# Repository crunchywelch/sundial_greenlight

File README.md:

# Sundial Greenlight

Terminal-based QC (Quality Control) application for audio cable testing and inventory management.

## Quick Start

### Setup Virtual Environment

```bash
# IMPORTANT: Must be SOURCED, not executed!
source dev_env.sh
```

**Why source instead of execute?**
- Running `./dev_env.sh` activates the venv in a subshell that closes immediately
- Sourcing with `source dev_env.sh` activates it in your current shell session

### Run the Application

```bash
python -m greenlight.main
```

On startup:
1. Splash screen displays with operator list
2. Select your operator number
3. You land on the scan hub: scan a cable to look it up or test it, or press
   a key for intake, inventory, orders, registration codes and labels

### Deactivate Virtual Environment

```bash
deactivate
```

## Features

### Cable Intake
Record pre-labelled cables against a SKU (press `r` at the scan hub):
1. Choose cable type (series → pattern → length → connector, or MISC/LTD)
2. Scan barcode with Zebra DS2208 scanner
3. Confirm serial number on screen
4. Press Enter to save to database
5. Scanner ready for next cable
6. Type 'q' + Enter to finish and see summary

### Test Cables
Scan a cable at the hub to run QC tests:
- Arduino-based electrical testing (continuity, resistance, XLR shell bond)
- Automatic pass/fail determination
- Results saved to database

### Other Features
- **Inventory** dashboard, LTD editions, dealer stock
- **Orders**: customer lookup and order fulfillment
- **Wholesale** registration codes, wire labels, box/UPC labels

## Repository Layout

| Path | What lives there |
|---|---|
| `greenlight/` | The terminal app |
| `shopify_app/` | Shopify Remix app + extensions |
| `catalog/` | Hand-edited product catalog YAML (the source of truth) |
| `data/` | Generated output and vendor input files |
| `tools/` | Admin and back-office scripts, grouped by area |
| `tests/` | SKU parity test + fixtures; `integration/` hits live services |
| `services/` | systemd units |
| `arduino/`, `ArduinoApps/` | Cable tester firmware and hardware docs |

## Testing

```bash
pytest                               # Python tests, no DB or network needed
(cd shopify_app && npm test)         # JS resolver against the same fixtures
```

Scripts in `tests/integration/` write to the live database / Shopify, so
pytest skips them unless `GREENLIGHT_RUN_INTEGRATION=1` is set. Read them
before running.

## Testing the Scanner

```bash
python tools/scanner/scantest.py
```

## Database Setup

See `tools/audio/schema.sql` for the database schema.

## Configuration

Edit `.env` for database settings and hardware flags (`GREENLIGHT_*`).
Operators are listed in `greenlight/config.py`.

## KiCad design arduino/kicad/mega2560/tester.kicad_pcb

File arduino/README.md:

# Arduino Cable Tester

This directory contains the Arduino firmware for the Greenlight Cable Testing system.

## Files

### Main Firmware
- **`cable_tester.ino`** - Complete Arduino sketch for ATmega32
- **`CableTester.h`** - Arduino library header (for future modular development)

### Documentation  
- **`HARDWARE_SETUP.md`** - Detailed hardware requirements and circuit diagrams
- **`README.md`** - This file

## Quick Start

### 1. Hardware Setup
1. Connect Arduino Mega 2560 to Raspberry Pi via USB
2. Build test circuit according to `HARDWARE_SETUP.md`
3. Connect cable test fixture to designated pins

### 2. Upload Firmware
**Using arduino-cli (Recommended):**
```bash
cd arduino
arduino-cli compile --fqbn arduino:avr:mega cable_tester
arduino-cli upload -p /dev/ttyACM0 --fqbn arduino:avr:mega cable_tester
```

**Using Arduino IDE:**
1. Open `cable_tester/cable_tester.ino` in Arduino IDE
2. Select Board: "Arduino Mega or Mega 2560"
3. Select correct COM port: /dev/ttyACM0
4. Click Upload

### 3. Test Communication
1. Open Serial Monitor (9600 baud)
2. Send command: `GET_UNIT_ID`
3. Should receive: `UNIT_ID:1`
4. Send command: `GET_STATUS`
5. Should receive: `STATUS:READY:FIXTURE_EMPTY:VOLTAGE_X.XX`

## Supported Commands

| Command | Description | Response |
|---------|-------------|----------|
| `GET_UNIT_ID` | Get Arduino unit identifier | `UNIT_ID:1` |
| `GET_STATUS` | Get system status | `STATUS:READY:FIXTURE_EMPTY:VOLTAGE_4.98` |
| `TEST_CABLE` | Run complete cable test | `TEST_RESULT:CONTINUITY:1:RESISTANCE:0.245:CAPACITANCE:156.2:POLARITY:1:OVERALL:1` |
| `CALIBRATE` | Run calibration sequence | `CALIBRATION:COMPLETE:VOLTAGE_CAL:1.0023:...` |
| `RESET` | Reset test circuit | `RESET:COMPLETE` |
| `SELF_TEST` | Run power-on self test | `SELF_TEST:PASS:VOLTAGE:4.98` |

## Test Result Format

The Arduino returns test results in a structured format:

```
TEST_RESULT:CONTINUITY:1:RESISTANCE:0.245:CAPACITANCE:156.2:POLARITY:1:OVERALL:1
```

**Fields:**
- **CONTINUITY**: 1 = all connections good, 0 = open circuit detected
- **RESISTANCE**: DC resistance in ohms (e.g., 0.245Ω)  
- **CAPACITANCE**: Cable capacitance in picofarads (e.g., 156.2pF)
- **POLARITY**: 1 = correct, 0 = reversed
- **OVERALL**: 1 = pass, 0 = fail

## Hardware Requirements

### Arduino Board
- **Arduino Mega 2560 R3** (official or compatible clone)
- Built-in USB connection (no external adapter needed)
- Provides excellent memory headroom:
  - 253KB Flash (4% used)
  - 8KB RAM (21% used)
  - 54 Digital I/O pins
  - 16 Analog inputs

### Circuit Components
- 3x 5V SPDT relays (continuity switching)
- Basic test circuit (see HARDWARE_SETUP.md)
- 4x LEDs for status indication
- Cable test fixture with insertion detection

### Recommended Components
- Precision current source for resistance measurement
- RC timing circuit for capacitance measurement
- Voltage reference for calibration
- ESD protection on all inputs

## Calibration

### Automatic Calibration
1. Send `CALIBRATE` command
2. Follow prompts for short circuit and open circuit connections
3. Calibration values are automatically calculated and stored

### Manual Calibration Values
You can adjust these constants in the code if needed:
```cpp
const float CONTINUITY_THRESHOLD_OHMS = 5.0;
const float VOLTAGE_REF = 5.0;
const float TEST_CURRENT_MA = 1.0;
```

## Troubleshooting

### No Response from Arduino
- Check USB connection and COM port
- Verify 9600 baud rate in Serial Monitor
- Check power LED on Arduino board

### Incorrect Test Results
- Run `SELF_TEST` command to verify hardware
- Check test fixture connections
- Run `CALIBRATE` to update calibration values
- Verify relay operation with multimeter

### Communication Errors
- Ensure clean 5V power supply
- Check for electrical noise interference  
- Verify all ground connections
- Consider USB isolation if needed

## Integration with Raspberry Pi

The Arduino communicates with the Raspberry Pi via USB serial. The Python code in the main project handles:

- Automatic Arduino detection on `/dev/ttyUSB*` ports
- Command/response protocol implementation
- Error handling and retries
- Integration with the Greenlight Terminal UI

## Development Notes

### Adding New Test Functions
1. Add command handling in `handleSerialCommand()`
2. Implement test function following existing patterns
3. Update response format documentation
4. Test with Python integration code

### Modifying Pin Assignments
1. Update pin definitions at top of `cable_tester.ino`
2. Update `HARDWARE_SETUP.md` documentation
3. Verify no pin conflicts with Arduino requirements

### Performance Optimization
- Adjust `MEASUREMENT_SAMPLES` for speed vs accuracy trade-off
- Modify delay times in test sequences as needed
- Consider interrupt-driven communication for faster response

## Production Deployment

### Quality Control
- Verify calibration accuracy with known standards
- Test all relay operations under load
- Validate measurement ranges with precision instruments
- Perform temperature stability testing

### Maintenance
- Monthly calibration verification
- Semi-annual precision component check  
- Annual full system validation
- Keep spare Arduino programmed and ready

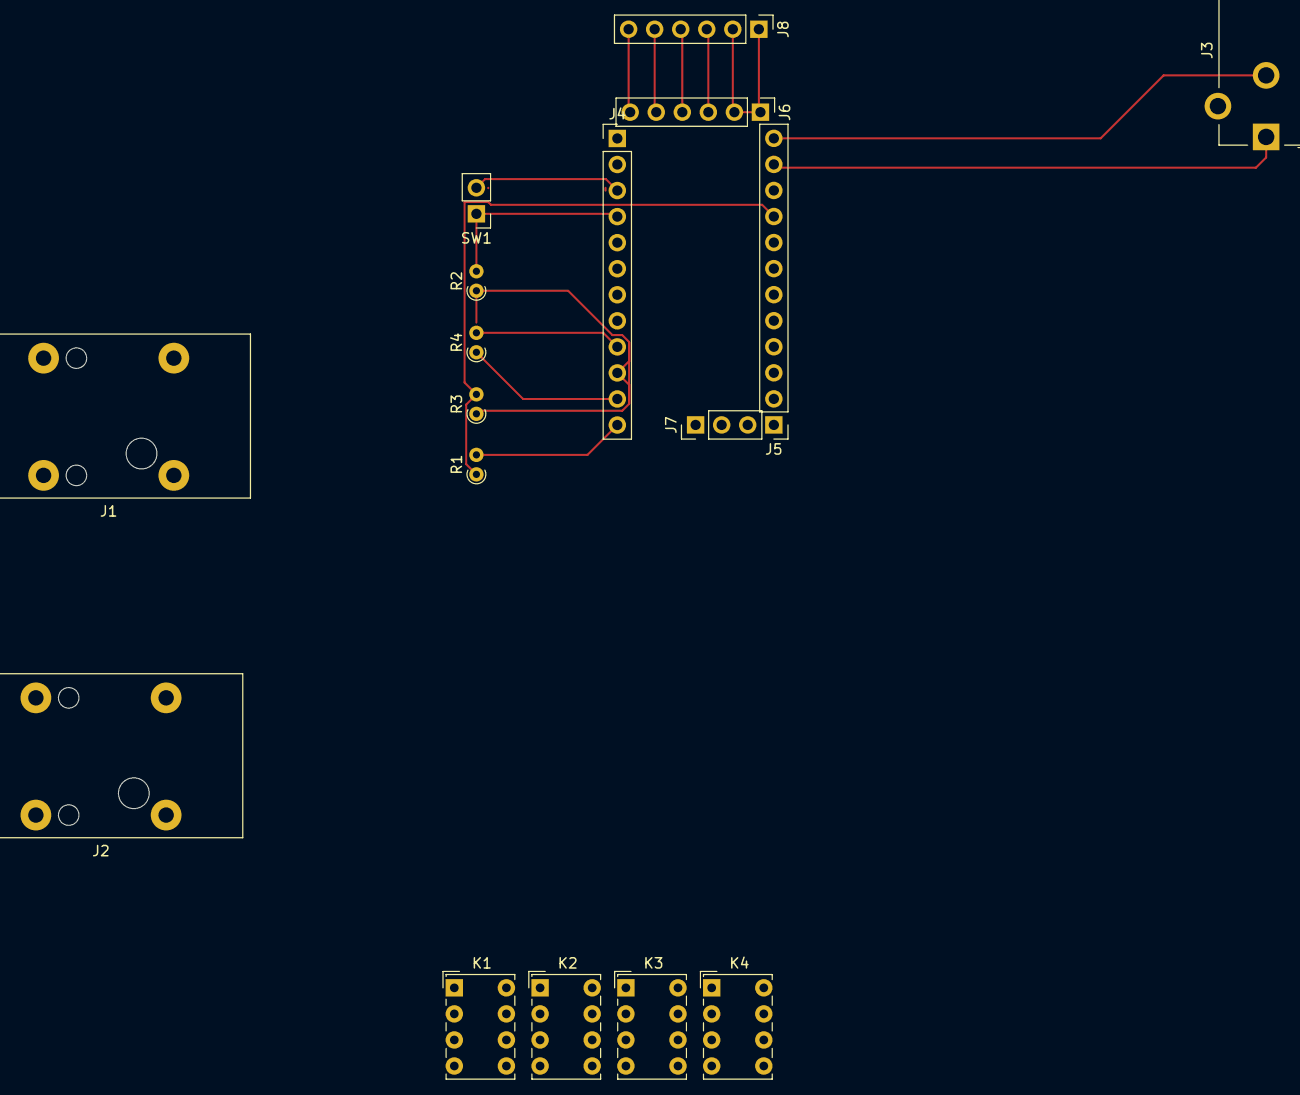
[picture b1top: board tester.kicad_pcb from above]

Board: 2 copper layers, 17 parts (0 on the bottom side), 12 nets.

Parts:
J1, J2: AudioJack2; Jack_6.35mm_Neutrik_NRJ4HF_Horizontal
J3: Barrel_Jack; BarrelJack_CUI_PJ-102AH_Horizontal
J4, J5: Conn_01x12; PinHeader_1x12_P2.54mm_Vertical
J6: Conn_01x06; PinHeader_1x06_P2.54mm_Vertical
J7: Conn_01x03; PinHeader_1x03_P2.54mm_Vertical
J8: Conn_01x06_Pin; PinHeader_1x06_P2.54mm_Vertical
K1, K2, K3, K4: Relay_DPDT; Relay_DPDT_Omron_G6K-2P
R1, R4: R10K; R_Axial_DIN0204_L3.6mm_D1.6mm_P1.90mm_Vertical
R2: R3.1K; R_Axial_DIN0204_L3.6mm_D1.6mm_P1.90mm_Vertical
R3: R1.8k; R_Axial_DIN0204_L3.6mm_D1.6mm_P1.90mm_Vertical
SW1: SW_Push; PinHeader_1x02_P2.54mm_Vertical

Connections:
/D6: J4.9, R4.2
/D7: J4.10, R2.1, R3.1
/D8: J4.11, R4.1
/DTR: J6.6, J8.6
/GND: J4.4, J6.1, J6.2, J8.1, J8.2, R2.2, SW1.1
/RST: J4.3, SW1.2
/RX1: J6.4, J8.4
/TX0: J6.5, J8.5
/VCC: J5.9, J6.3, J8.3, R1.1, R3.2
unnamed: J4.12, R1.2
unnamed: J3.1, J5.11
unnamed: J3.2, J5.12

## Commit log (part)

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2025-08-01 checking in
2025-08-02 pre-claude modifications
2025-08-05 db handling update
2025-08-07 leaving debian
2025-08-07 moving tests
2025-08-08 brady stuff
2025-09-08 arduino tester v1
2025-09-10 arduino work
2025-10-31 remove brady
2025-11-09 cleanup
2025-11-09 working scanner implementation more cleanup
2025-12-31 shopify and much else
2025-12-31 shopify and other stuff
2026-01-01 adding mosquitto for scanner
2026-01-01 adding post to shopify endpopint for scanner daemon
2026-01-02 some arduino work, update scanner daemon to post to dev and prod
2026-01-02 shopify: ignore node and build, move to prod
2026-01-02 some deploy fixes, don't poll when text fields don't have focus
2026-01-04 add resistance check
2026-02-20 small
2026-02-20 add greenlight.sh for windows shortcut
2026-02-23 add order cable assignment block functionality
2026-02-24 update sku defs
2026-02-28 install arduino ide if not found
2026-03-04 asset valuation fixes, start uno Q port
2026-03-04 clean up arduino docs, add kicad files
2026-03-04 add uno q docs
2026-03-09 update 3-9 snapshots
2026-03-09 kicad updates, puzzle light map, more util updates
2026-03-10 kicad and pricing util
2026-03-13 add shopify user id to scan event webhooks
2026-03-16 update printer stuff, add barcode label function
2026-03-17 add special baby assignment handling
2026-03-17 update sqlite db
2026-03-17 spokky script
2026-03-19 update valuation db
2026-03-21 add cable images
2026-06-12 add sean
